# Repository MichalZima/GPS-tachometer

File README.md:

This is my first project on github and also first time I am working with git and github.

My project is GPS tracking device, with a mobile app, which visualize data from device.
This device was made as bicycle tachometer but you can use it for basically anything from running to flying, because the measuring is done with GPS

I made device with arduino and it's components are:
	- measuring Speed, Distance (total and per day/session), Height above sea level, Climbing (total and per day/session), which is all printed on devices display
	- measuring  Lattitude and Longitude to draw our route to a map in mobile app
			
Device is not finished yet but I have functional prototype.

Now I am working on app and I'll finish the device later

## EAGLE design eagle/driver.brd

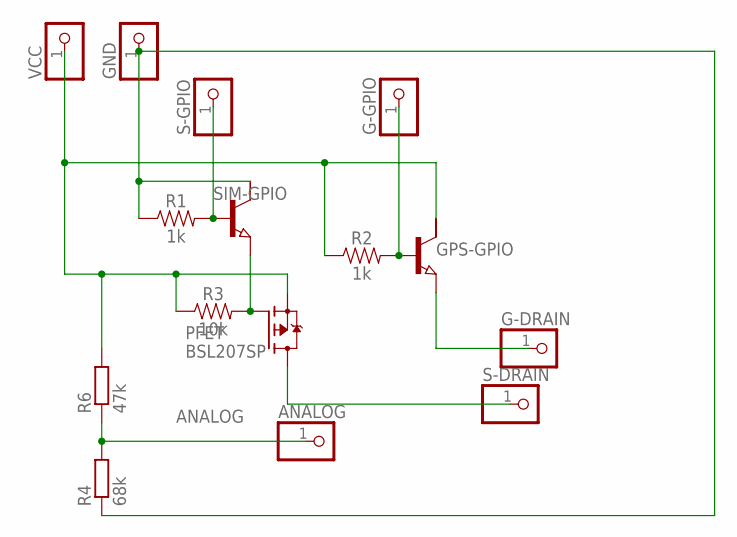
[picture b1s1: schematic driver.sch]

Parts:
ANALOG: PINHD-1X1; 1X01
G-DRAIN: PINHD-1X1; 1X01
G-GPIO: PINHD-1X1; 1X01
GND: PINHD-1X1; 1X01
GPS-GPIO: NPN-TRANSISTIOR-2COLSOT89; SOT89
PFET: BSL207SP; SC74_INFINEON
R1, R2: 1k; 0603
R3: 10k; 0603
R4: 68k; 0204/7
R6: 47k; 0204/7
S-DRAIN: PINHD-1X1; 1X01
S-GPIO: PINHD-1X1; 1X01
SIM-GPIO: NPN-TRANSISTIOR-2COLSOT89; SOT89
VCC: PINHD-1X1; 1X01

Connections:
ANALOG: ANALOG.1, R4.2, R6.1
unnamed: PFET.3 (G), R3.2, SIM-GPIO.3 (E)
unnamed: G-GPIO.1, GPS-GPIO.1 (B), R2.2
unnamed: GPS-GPIO.2 (C), PFET.4 (S), R2.1, R3.1, R6.2, VCC.1
unnamed: R1.2, S-GPIO.1, SIM-GPIO.1 (B)
unnamed: G-DRAIN.1, GPS-GPIO.3 (E)
unnamed: PFET.1 (D), PFET.2 (D), PFET.5 (D), PFET.6 (D), S-DRAIN.1
unnamed: GND.1, R1.1, R4.1, SIM-GPIO.2 (C)

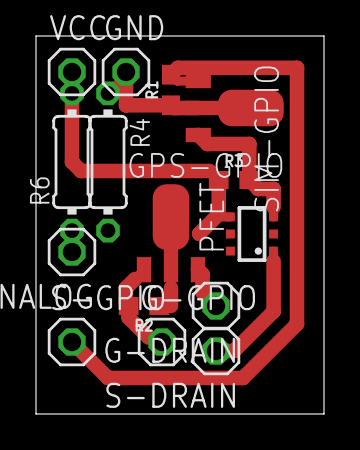
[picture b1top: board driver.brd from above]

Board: 2 copper layers, 16.0 x 21.0 mm, 15 parts (0 on the bottom side), 8 nets.

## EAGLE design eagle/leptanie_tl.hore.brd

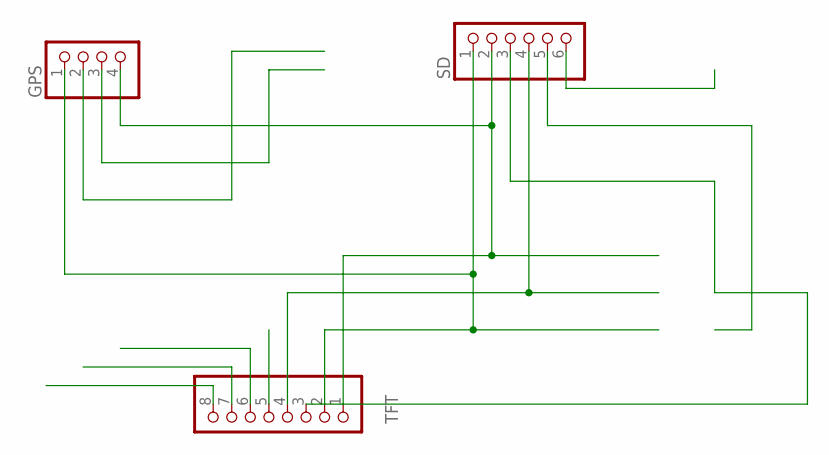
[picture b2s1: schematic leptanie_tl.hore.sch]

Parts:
GPS: PINHD-1X4; 1X04
SD: PINHD-1X6; 1X06
TFT: PINHD-1X8; 1X08

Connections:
MOSI: SD.4, TFT.4
unnamed: SD.3, TFT.3
unnamed: GPS.4, SD.2, TFT.1
S: GPS.1, SD.1, TFT.2

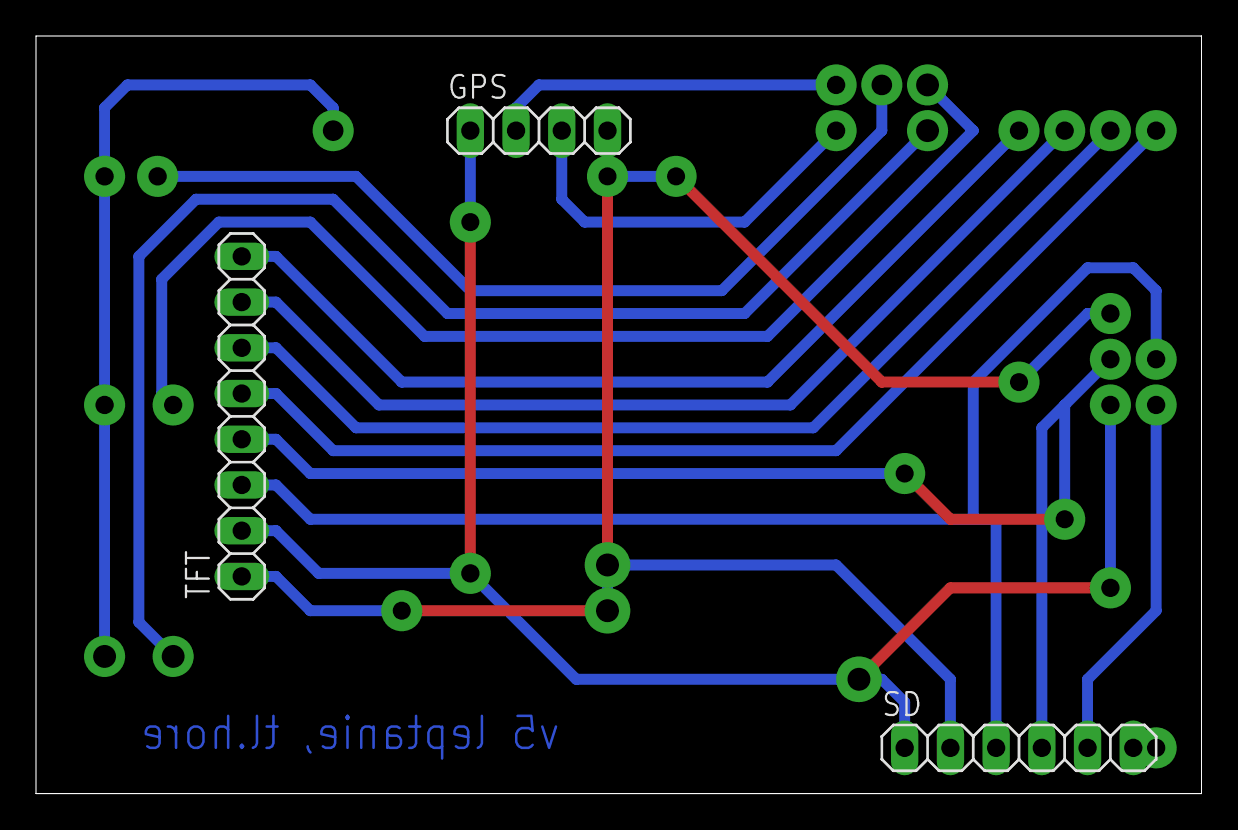
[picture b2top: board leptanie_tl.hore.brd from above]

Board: 2 copper layers, 64.8 x 42.1 mm, 3 parts (0 on the bottom side), 4 nets.

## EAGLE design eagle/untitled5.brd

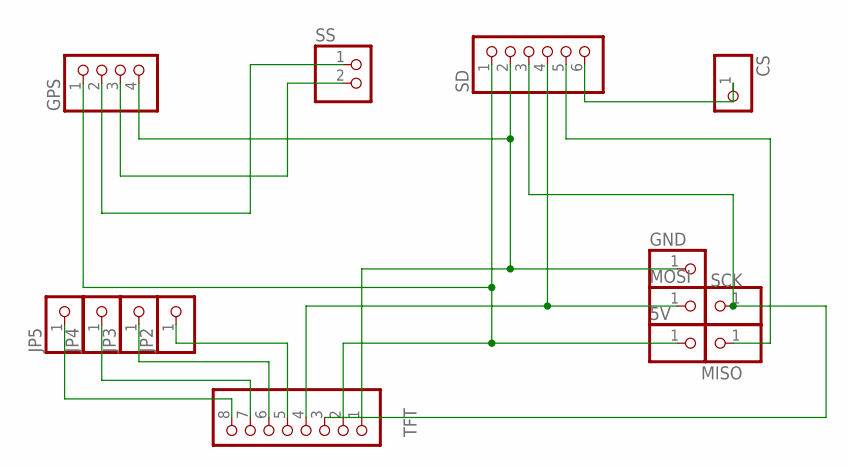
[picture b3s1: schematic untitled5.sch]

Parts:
5V: PINHD-1X1; 1X01
CS: PINHD-1X1; 1X01
GND: PINHD-1X1; 1X01
GPS: PINHD-1X4; 1X04
JP2, JP3, JP4, JP5: PINHD-1X1; 1X01
MISO: PINHD-1X1; 1X01
MOSI: PINHD-1X1; 1X01
SCK: PINHD-1X1; 1X01
SD: PINHD-1X6; 1X06
SS: PINHD-1X2; 1X02
TFT: PINHD-1X8; 1X08

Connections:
MOSI: MOSI.1, SD.4, TFT.4
unnamed: CS.1, SD.6
unnamed: MISO.1, SD.5
unnamed: JP2.1, TFT.5
unnamed: SCK.1, SD.3, TFT.3
unnamed: GND.1, GPS.4, SD.2, TFT.1
unnamed: JP3.1, TFT.6
unnamed: GPS.2, SS.1
unnamed: GPS.3, SS.2
unnamed: JP4.1, TFT.7
unnamed: JP5.1, TFT.8
S: 5V.1, GPS.1, SD.1, TFT.2

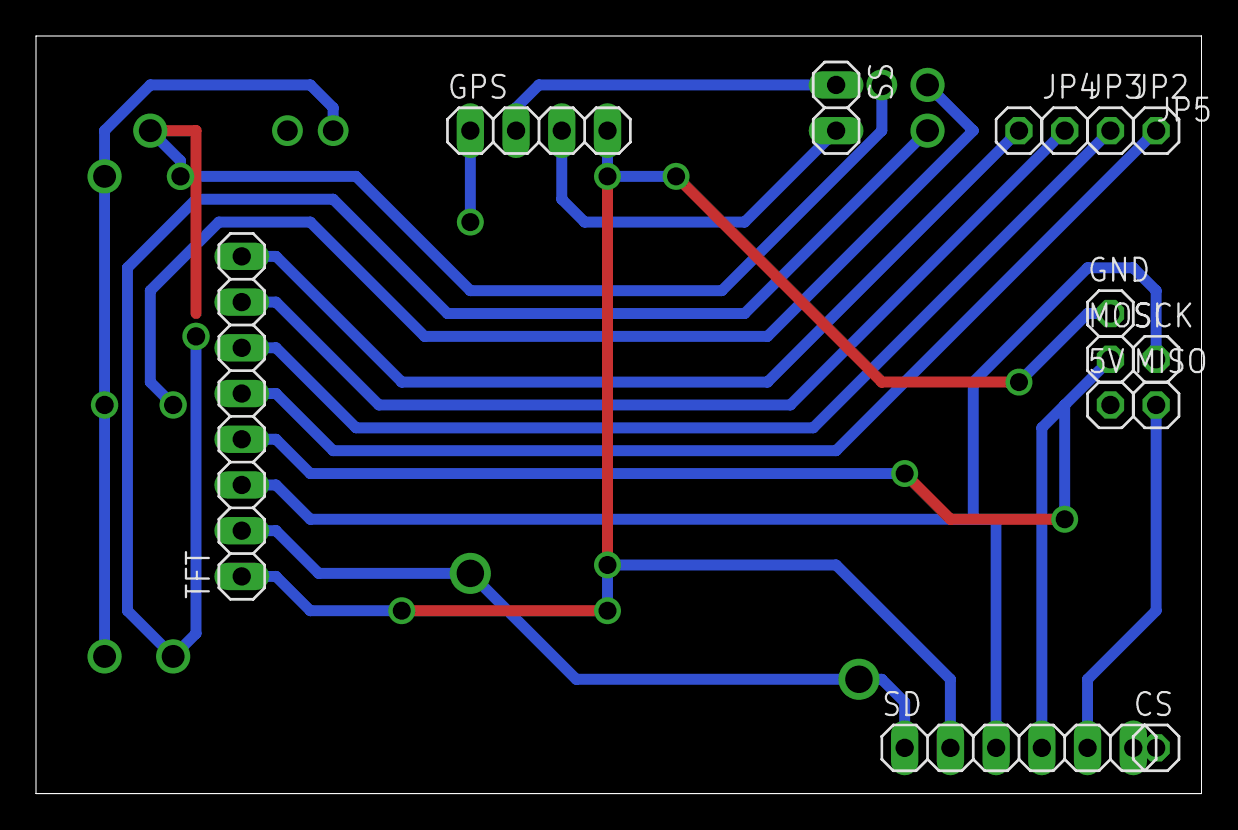
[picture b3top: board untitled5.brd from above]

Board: 2 copper layers, 64.8 x 42.1 mm, 14 parts (0 on the bottom side), 12 nets.

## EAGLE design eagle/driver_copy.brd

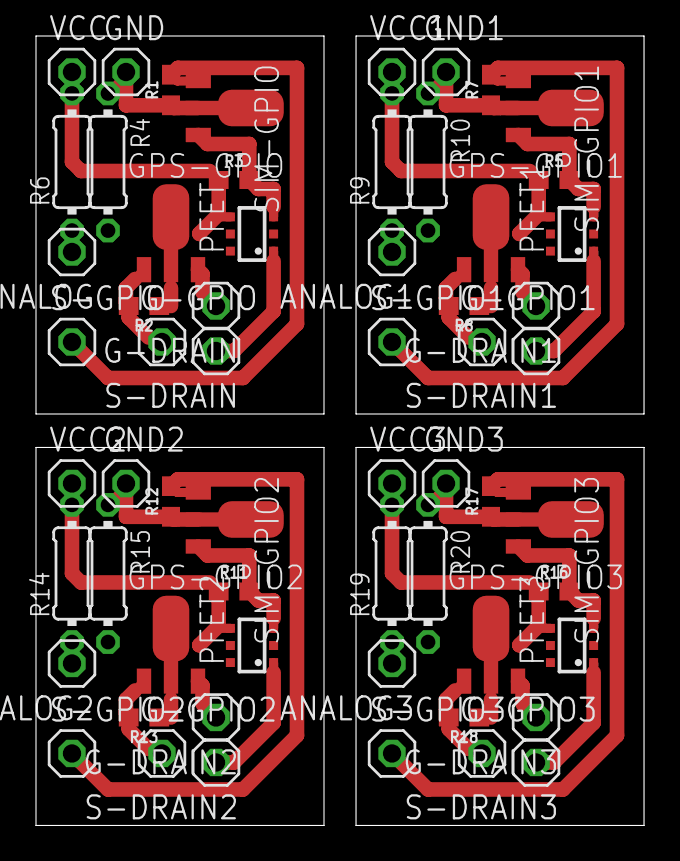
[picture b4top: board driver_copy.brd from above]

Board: 2 copper layers, 33.8 x 43.9 mm, 60 parts (0 on the bottom side), 32 nets.

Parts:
ANALOG, ANALOG1, ANALOG2, ANALOG3: 1X01
G-DRAIN, G-DRAIN1, G-DRAIN2, G-DRAIN3: 1X01
G-GPIO, G-GPIO1, G-GPIO2, G-GPIO3: 1X01
GND, GND1, GND2, GND3: 1X01
GPS-GPIO, GPS-GPIO1, GPS-GPIO2, GPS-GPIO3: SOT89
PFET, PFET1, PFET2, PFET3: BSL207SP; SC74_INFINEON
R1, R2, R7, R8, R12, R13, R17, R18: 1k; 0603
R3, R5, R11, R16: 10k; 0603
R4, R10, R15, R20: 68k; 0204/7
R6, R9, R14, R19: 47k; 0204/7
S-DRAIN, S-DRAIN1, S-DRAIN2, S-DRAIN3: 1X01
S-GPIO, S-GPIO1, S-GPIO2, S-GPIO3: 1X01
SIM-GPIO, SIM-GPIO1, SIM-GPIO2, SIM-GPIO3: SOT89
VCC, VCC1, VCC2, VCC3: 1X01

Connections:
ANALOG: ANALOG.1, R4.2, R6.1
ANALOG1: ANALOG1.1, R9.1, R10.2
ANALOG2: ANALOG2.1, R14.1, R15.2
ANALOG3: ANALOG3.1, R19.1, R20.2
unnamed: PFET.3, R3.2, SIM-GPIO.3
unnamed: G-GPIO.1, GPS-GPIO.1, R2.2
unnamed: GPS-GPIO.2, PFET.4, R2.1, R3.1, R6.2, VCC.1
unnamed: R1.2, S-GPIO.1, SIM-GPIO.1
unnamed: G-DRAIN.1, GPS-GPIO.3
unnamed: PFET.1, PFET.2, PFET.5, PFET.6, S-DRAIN.1
unnamed: GND.1, R1.1, R4.1, SIM-GPIO.2
unnamed: PFET1.3, R5.2, SIM-GPIO1.3
unnamed: R7.2, S-GPIO1.1, SIM-GPIO1.1
unnamed: G-GPIO1.1, GPS-GPIO1.1, R8.2
unnamed: G-DRAIN1.1, GPS-GPIO1.3
unnamed: PFET1.1, PFET1.2, PFET1.5, PFET1.6, S-DRAIN1.1
unnamed: GPS-GPIO1.2, PFET1.4, R5.1, R8.1, R9.2, VCC1.1
unnamed: GND1.1, R7.1, R10.1, SIM-GPIO1.2
unnamed: PFET2.3, R11.2, SIM-GPIO2.3
unnamed: R12.2, S-GPIO2.1, SIM-GPIO2.1
unnamed: G-GPIO2.1, GPS-GPIO2.1, R13.2
unnamed: G-DRAIN2.1, GPS-GPIO2.3
unnamed: PFET2.1, PFET2.2, PFET2.5, PFET2.6, S-DRAIN2.1
unnamed: GPS-GPIO2.2, PFET2.4, R11.1, R13.1, R14.2, VCC2.1
unnamed: GND2.1, R12.1, R15.1, SIM-GPIO2.2
unnamed: PFET3.3, R16.2, SIM-GPIO3.3
unnamed: R17.2, S-GPIO3.1, SIM-GPIO3.1
unnamed: G-GPIO3.1, GPS-GPIO3.1, R18.2
unnamed: G-DRAIN3.1, GPS-GPIO3.3
unnamed: PFET3.1, PFET3.2, PFET3.5, PFET3.6, S-DRAIN3.1
unnamed: GPS-GPIO3.2, PFET3.4, R16.1, R18.1, R19.2, VCC3.1
unnamed: GND3.1, R17.1, R20.1, SIM-GPIO3.2

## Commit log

2020-06-01 Changes to be committed:
2020-06-01 changing files in directory
2020-06-01 removed useless files
2020-07-17 update main1
2020-07-17 added version for arduino mega
2020-07-17 deleted gps_main1
2020-07-17 modified .gitignore
2020-12-14 made pcbs for mega shield
2020-12-14 modified pcbs
2020-12-14 second version of pcb
2020-12-14 added scheme for esp8266
2020-12-15 modified main_MEGA
2020-12-15 modified main NANO
2020-12-15 made code version for esp8266
2020-12-15 convert code to OOP for esp 12e
2020-12-15 modified Buttons class
2020-12-15 modified main
2020-12-15 fix screens
2020-12-15 edit edit
2020-12-15 modified
2020-12-15 edit
2020-12-15 working on trafic
2020-12-15 tft class edit
2020-12-15 edit tft class
2020-12-15 removed bugs
2020-12-16 edit directory
2020-12-17 merged from test
2020-12-17 added some variables
2020-12-17 updated coordinates saving
2020-12-17 working on saving data
2020-12-17 modified classes
2020-12-18 debugged
2020-12-18 debugging
2020-12-19 working on time zone
2020-12-19 editting traffic
2020-12-19 set time zone
2020-12-19 added time zone value to gps time
2020-12-21 adding time zone settings
2020-12-21 adding time saving
2020-12-21 real time printing
2020-12-22 debugged and restored to good version
2020-12-22 edit distance calculating
2020-12-22 edit data values saving
2020-12-22 nothing
2020-12-22 made test functions for printing values
2020-12-22 repaired small bugs
2020-12-22 observing data
2020-12-22 printed age for test
2020-12-23 made clearer print
2020-12-23 added data to save
2020-12-23 printed more data
2020-12-26 edit saving to more frequent
2020-12-26 edit data save function
2020-12-26 edit saving condition
2020-12-26 repaired saving bugs
2020-12-26 changed conditions for saving
2020-12-28 made statement when print data
2020-12-28 edit statement
2020-12-28 edit condition for printing distance
2020-12-28 wait for updating data to save
2020-12-28 added state of update to save
2020-12-28 saving chsr passed statement
2020-12-28 repaired saving coordinates bug
2020-12-28 removed smartDelay
2020-12-29 added class for main screens
2020-12-29 just little irrelevant changes
2020-12-29 editing structure of main loop
2020-12-29 moved printing main screens to Screens class
2020-12-29 decentralized methodes and code parts to different objects
2020-12-29 modified screens object
2020-12-29 changed measuring pass logic
2020-12-30 added methods for calculating average
2020-12-30 added more variables to save
2020-12-30 changed logic for delaying calculating
2021-01-02 editing items in menu
2021-01-02 edit if statement for saving data
2021-01-04 just small edit
2021-01-04 removed some data to save
2021-01-04 saving temporarily gps data
2021-01-04 changing if statement for saving
2021-01-04 saving temporarily gps data 1. test
2021-01-04 small edit saving temporarily gps data 1. test
2021-01-04 saving temp data to SD for observation
2021-01-04 saving full temp data to SD
2021-01-04 printing full temp date
2021-01-05 small changes
2021-01-05 changing logic back to passLoops
2021-01-05 put temp data saving in smartDelay function
2021-01-05 changed if statement for saving
2021-01-05 removed temporary saving data
2021-01-05 removed tempSavedData from saving to SD
2021-01-06 made errorCheck function
2021-01-06 edit pass function
2021-01-06 maybe solved signal and errors problem
2021-01-07 making it work
2021-01-07 it works
2021-01-09 testing and upgrading
2021-01-09 finishing version 2.0.0
2021-01-09 finished version, need proper testing
2021-01-09 editing menu
2021-01-09 start stop track
2021-01-09 graphic stuff for track item done for now
2021-01-09 v3.1.0
2021-01-09 edit description in main
2021-01-09 debugged v3.1.0
2021-01-11 finished v3.1.0
2021-01-11 changed course difference for saving data
2021-01-11 made function to check if date is valid
2021-01-11 aplication of date check
2021-01-11 removed passed and failed checksum from saving
2021-01-11 chenged data saving paths
2021-01-12 edit printValuesForObservation method
2021-01-12 edit saving path
2021-01-12 just little edit
2021-01-12 track and noTrack modes
2021-01-12 saving no track data
2021-01-12 finished date check
2021-01-12 turnOff logic
2021-01-12 changing between daily and track measuring
2021-01-12 power off logic
2021-01-12 added startup object
2021-01-12 made powerOff logic
2021-01-12 startup check and backup
2021-01-12 backup load logic
2021-01-12 backup saving
2021-01-12 counting daily or track or total distance
2021-01-12 backup and startup working
2021-01-13 startup logic and loading
2021-01-13 made loading bar
2021-01-13 init check and loading bar finished
2021-01-13 working on backup uploading
2021-01-13 almost done
2021-01-13 backup read done
2021-01-14 backup and non backup initial load
2021-01-15 load backup
2021-01-15 done
2021-01-16 v3.2 load and backup done
2021-01-16 pover saving screen off
2021-01-18 edit power saving (screen off)
2021-01-18 edit saving template
2021-01-18 edit gitignore
2021-01-26 working on pcb
2021-01-26 added deepSleep mode
2021-01-26 removed deepSleep
2021-01-28 made PCB
2021-01-28 added wifi item in menu
2021-01-28 just small necessary changes
2021-01-28 added objects for FTP data sending
2021-01-28 pandas testing app
2021-01-29 app for gps tracker
2021-01-29 test script for downloading files from device
2021-01-29 knowing how server works
2021-01-29 modified gitignore
2021-02-09 edit pcb
2021-02-09 new pcb
2021-02-09 .py desktop app
2021-02-09 editing esp software
2021-03-30 added ttgo t4 version
2021-03-30 trying to make it work
2021-04-01 buttons work
2021-04-01 SD work
2021-04-01 display works
2021-04-01 menu and cursor works
2021-04-01 main works
2021-04-02 added screen turn off
2021-04-02 cursor works
2021-04-02 necessary edit
2021-04-06 changed default time zone
2021-04-06 small edit
2021-04-06 saving works
2021-04-06 necessary edits
2021-04-08 changed pins
2021-04-08 edit paths for saving and modified functions for esp32
2021-04-08 auto-screenoff OFF
2021-04-08 deleted backup function
2021-04-08 deleted unneccesary files and added new
2021-04-08 add deepsleep
2021-04-09 added server
2021-04-09 comment
2021-04-09 server on
2021-04-09 dufam ze to uz pojde xdd
2021-04-12 deleted
2021-04-12 modified deepSleep.h
2021-04-12 made class for sending data from sd
2021-04-12 edit menu for new butoon handler
2021-04-12 made multi handler
2021-04-12 small gps edit
2021-04-12 changed logic a bit
2021-04-12 deleted server for now
2021-04-14 debugging menu
2021-04-15 driver for modules
2021-04-16 saving in JSON format
2021-04-17 makeFile function
2021-04-17 adding variables and calculations
2021-04-17 edits
2021-04-22 added functions
2021-04-22 made inventor folder
2021-04-23 3D case parts
2021-04-26 3D cave v.2
2021-04-26 remade v.2
2021-05-10 made folder with data from SD

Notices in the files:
parts and their libraries:
SparkFun-Resistors: Licensing: Creative Commons ShareAlike 4.0 International - https://creativecommons.org/licenses/by-sa/4.0
